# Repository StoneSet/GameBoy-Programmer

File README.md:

# Gameboy USB programmer
## The Eagle project of the gameboy programmer project

**(c) Found the entire project here : http://reinerziegler.de.mirrors.gg8.se/readplus.htm**

## Included:
1. All needed files to modify the project
2. BOM

## Some img's :

------

# 

(c) Reiner Ziegler & StoneSet - http://reinerziegler.de.mirrors.gg8.se/readplus.htm - http://stoneset.github.io/ (2019)

plz do not steal, i'm not the owner of this project, i'm only the owner of this pcb. Have fun !

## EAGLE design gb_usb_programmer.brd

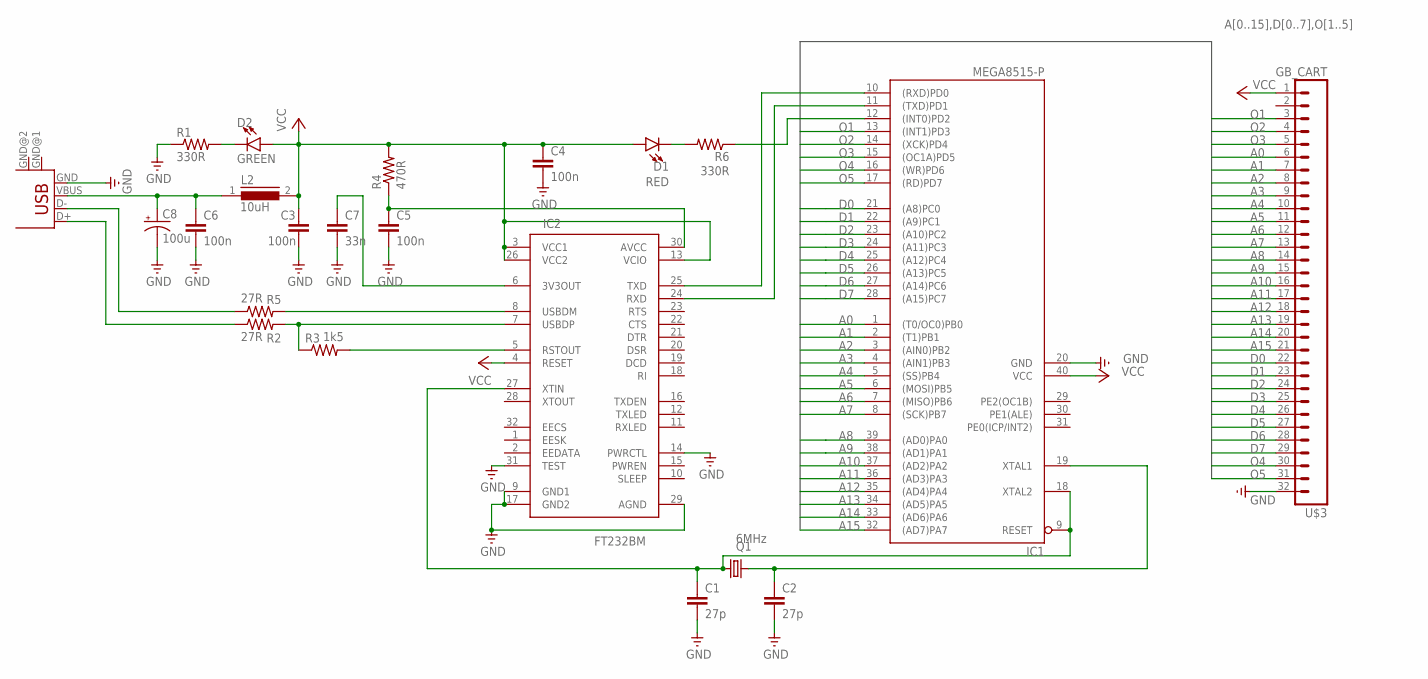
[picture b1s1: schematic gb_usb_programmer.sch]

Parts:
C1, C2: 27p; C5B2.5
C3, C4, C5, C6: 100n; C5B2.5
C7: 33n; C5B2.5
C8: 100u; E1,8-4
D1: RED; LED_5MM-KIT
D2: GREEN; LED_5MM-KIT
IC1: MEGA8515-P; DIL40
IC2: FT232BM; QFP-32
L2: 10uH; 82114R
Q1: 6MHz; HC49/S
R1, R6: 330R; 0207/10
R2, R5: 27R; 0207/10
R3: 1k5; 0207/10
R4: 470R; 0207/10
U$3: GB_CART; 1X32_GB
USB1: USB-B-H

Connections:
A0: IC1.1 ((T0/OC0)PB0), U$3.6
A1: IC1.2 ((T1)PB1), U$3.7
A2: IC1.3 ((AIN0)PB2), U$3.8
A3: IC1.4 ((AIN1)PB3), U$3.9
A4: IC1.5 ((SS)PB4), U$3.10
A5: IC1.6 ((MOSI)PB5), U$3.11
A6: IC1.7 ((MISO)PB6), U$3.12
A7: IC1.8 ((SCK)PB7), U$3.13
A8: IC1.39 ((AD0)PA0), U$3.14
A9: IC1.38 ((AD1)PA1), U$3.15
A10: IC1.37 ((AD2)PA2), U$3.16
A11: IC1.36 ((AD3)PA3), U$3.17
A12: IC1.35 ((AD4)PA4), U$3.18
A13: IC1.34 ((AD5)PA5), U$3.19
A14: IC1.33 ((AD6)PA6), U$3.20
A15: IC1.32 ((AD7)PA7), U$3.21
D0: IC1.21 ((A8)PC0), U$3.22
D1: IC1.22 ((A9)PC1), U$3.23
D2: IC1.23 ((A10)PC2), U$3.24
D3: IC1.24 ((A11)PC3), U$3.25
D4: IC1.25 ((A12)PC4), U$3.26
D5: IC1.26 ((A13)PC5), U$3.27
D6: IC1.27 ((A14)PC6), U$3.28
D7: IC1.28 ((A15)PC7), U$3.29
GND: C1.2, C2.2, C3.2, C4.2, C5.2, C6.2, C7.2, C8.-, IC1.20 (GND), IC2.9 (GND1), IC2.14 (PWRCTL), IC2.17 (GND2), IC2.29 (AGND), IC2.31 (TEST), R1.1, U$3.32, USB1.GND
unnamed: D1.K (C), R6.2
unnamed: D2.K (C), R1.2
unnamed: C6.1, C8.+, L2.1, USB1.VBUS
unnamed: C5.1, IC2.30 (AVCC), R4.1
unnamed: R2.1, USB1.D+
unnamed: R5.1, USB1.D-
unnamed: IC2.7 (USBDP), R2.2, R3.1
unnamed: IC2.8 (USBDM), R5.2
unnamed: IC2.5 (RSTOUT), R3.2
unnamed: C7.1, IC2.6 (3V3OUT)
unnamed: C2.1, IC1.19 (XTAL1), Q1.2
unnamed: C1.1, IC1.9 (RESET), IC1.18 (XTAL2), IC2.27 (XTIN), Q1.1
unnamed: IC1.10 ((RXD)PD0), IC2.25 (TXD)
unnamed: IC1.11 ((TXD)PD1), IC2.24 (RXD)
unnamed: IC1.12 ((INT0)PD2), R6.1
O1: IC1.13 ((INT1)PD3), U$3.3
O2: IC1.14 ((XCK)PD4), U$3.4
O3: IC1.15 ((OC1A)PD5), U$3.5
O4: IC1.16 ((WR)PD6), U$3.30
O5: IC1.17 ((RD)PD7), U$3.31
VCC: C3.1, C4.1, D1.A, D2.A, IC1.40 (VCC), IC2.3 (VCC1), IC2.4 (RESET), IC2.13 (VCIO), IC2.26 (VCC2), L2.2, R4.2, U$3.1

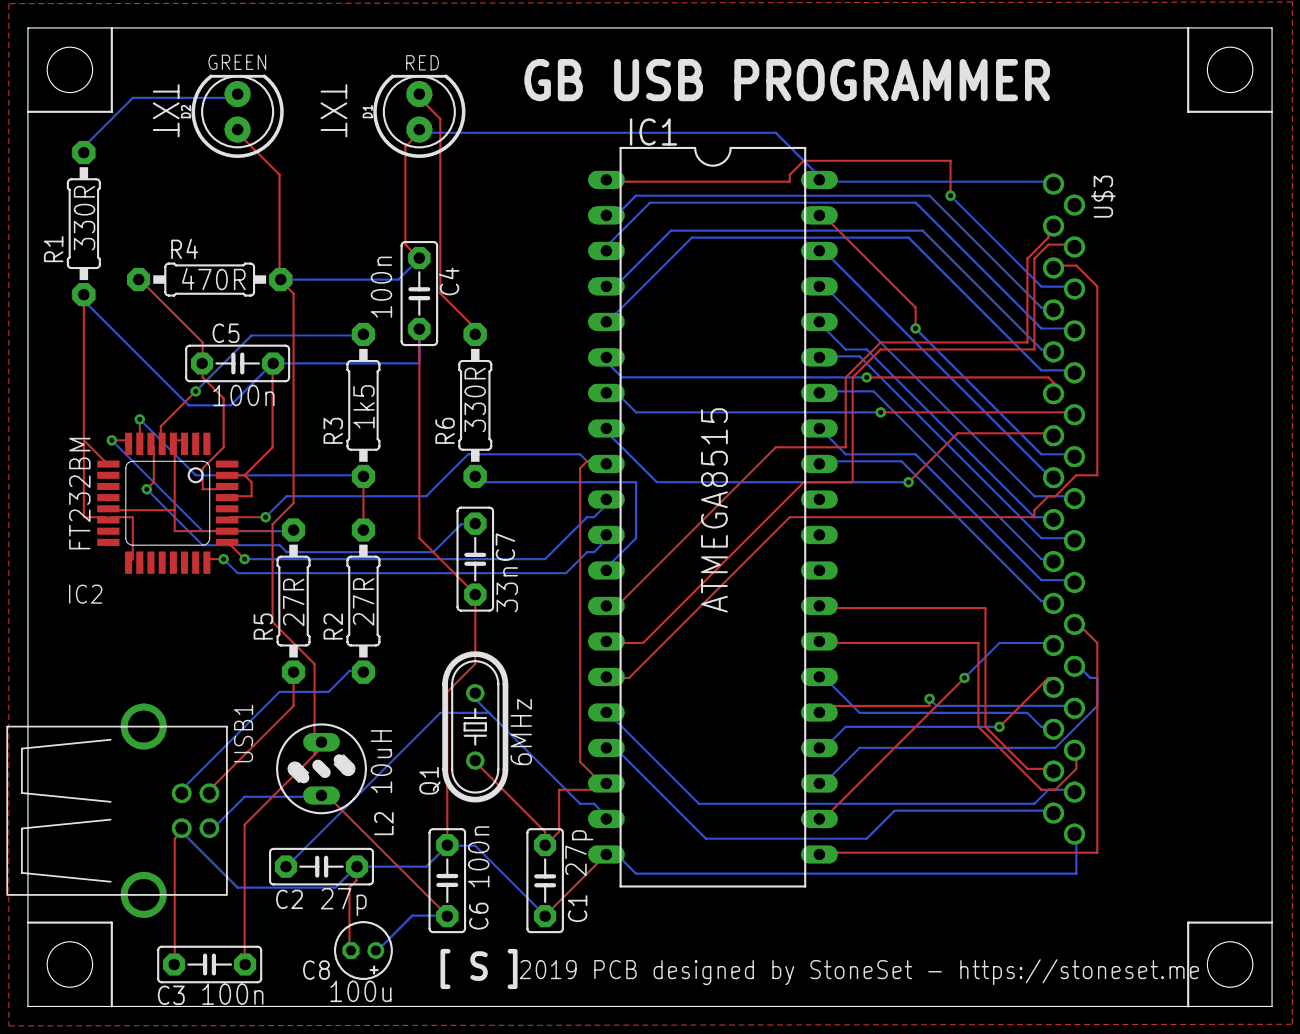
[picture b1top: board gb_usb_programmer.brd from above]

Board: 2 copper layers, 89.0 x 70.0 mm, 22 parts (0 on the bottom side), 46 nets.

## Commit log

2017-12-11 First release
    (yay!)
2017-12-11 moare feature
2017-12-11 Create readme.md
    wow
2019-04-24 [WIP] ! feat(project): move roject to eagle
    Don't use this version : unfinished

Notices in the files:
parts and their libraries:
SparkFun-LED: Licensing: Creative Commons ShareAlike 4.0 International - https://creativecommons.org/licenses/by-sa/4.0
ftdi2: FTDI USB-serial converters and FIFOs, © UNITRONIC AG
